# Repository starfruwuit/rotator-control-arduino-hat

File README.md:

# rotator-control-arduino-hat
hat to fit onto an Arduino MEGA 2560 R3 to connect a YAESU G550 rotator controller to input from SatNOGS
note: breadboard version uses 2N 2222 331 transistors: https://infodatasheet.com/2n2222a-331-datasheet.html

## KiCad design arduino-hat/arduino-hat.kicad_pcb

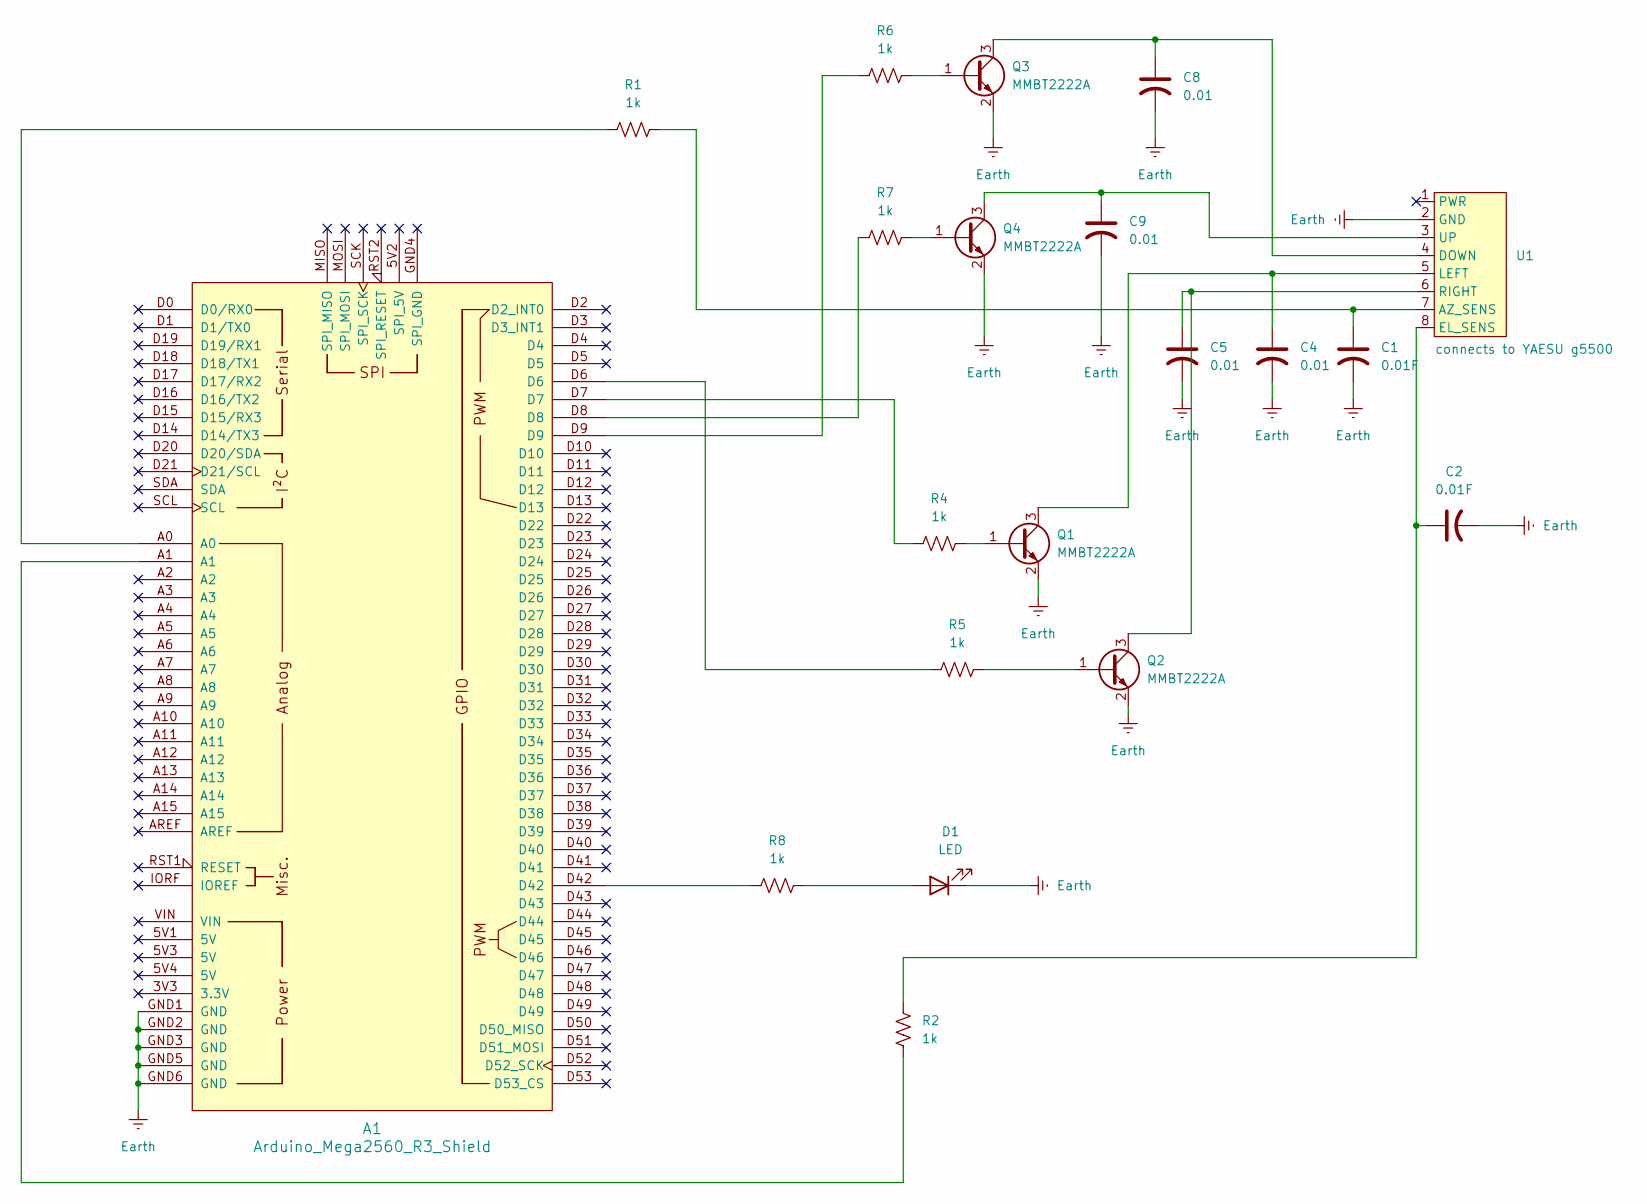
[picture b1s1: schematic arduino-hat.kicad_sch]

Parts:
A1: Arduino_Mega2560_R3_Shield; Arduino_Mega2560_R3_Shield_revised
C1, C2: 0.01F; C_0805_2012Metric_Pad1.18x1.45mm_HandSolder
C4, C5, C8, C9: 0.01; C_0805_2012Metric_Pad1.18x1.45mm_HandSolder
D1: LED; LED_1206_3216Metric_Pad1.42x1.75mm_HandSolder
Q1, Q2, Q3, Q4: MMBT2222A; SOT-23
R1, R2, R4, R5, R6, R7, R8: 1k; R_0603_1608Metric_Pad0.98x0.95mm_HandSolder
U1: PinHeader_1x08_P2.54mm_Vertical

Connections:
Earth: A1.GND1 (GND), A1.GND2 (GND), A1.GND3 (GND), A1.GND5 (GND), A1.GND6 (GND), C1.2, C2.2, C4.2, C5.2, C8.2, C9.2, D1.1 (K), Q1.2 (E), Q2.2 (E), Q3.2 (E), Q4.2 (E), U1.2 (GND)
unnamed: A1.A0, R1.1
unnamed: A1.A1, R2.2
unnamed: A1.D6, R5.1
unnamed: A1.D7, R4.1
unnamed: A1.D8, R7.1
unnamed: A1.D9, R6.1
unnamed: A1.D42, R8.2
unnamed: D1.2 (A), R8.1
unnamed: Q1.1 (B), R4.2
unnamed: C4.1, Q1.3 (C), U1.5 (LEFT)
unnamed: Q2.1 (B), R5.2
unnamed: C5.1, Q2.3 (C), U1.6 (RIGHT)
unnamed: Q3.1 (B), R6.2
unnamed: C8.1, Q3.3 (C), U1.4 (DOWN)
unnamed: Q4.1 (B), R7.2
unnamed: C9.1, Q4.3 (C), U1.3 (UP)
unnamed: C1.1, R1.2, U1.7 (AZ_SENS)
unnamed: C2.1, R2.1, U1.8 (EL_SENS)

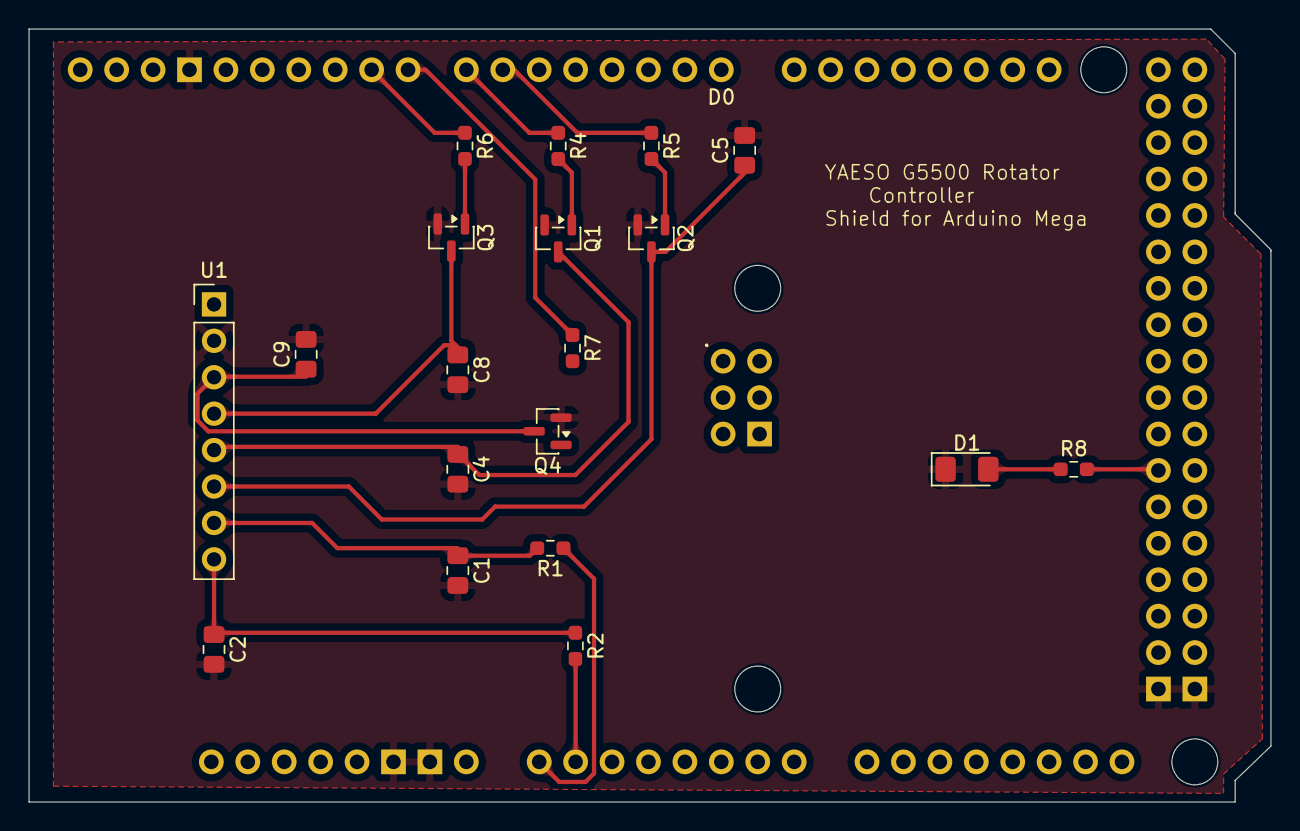
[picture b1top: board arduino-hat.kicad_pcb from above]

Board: 2 copper layers, 86.6 x 53.9 mm, 20 parts (0 on the bottom side), 19 nets.

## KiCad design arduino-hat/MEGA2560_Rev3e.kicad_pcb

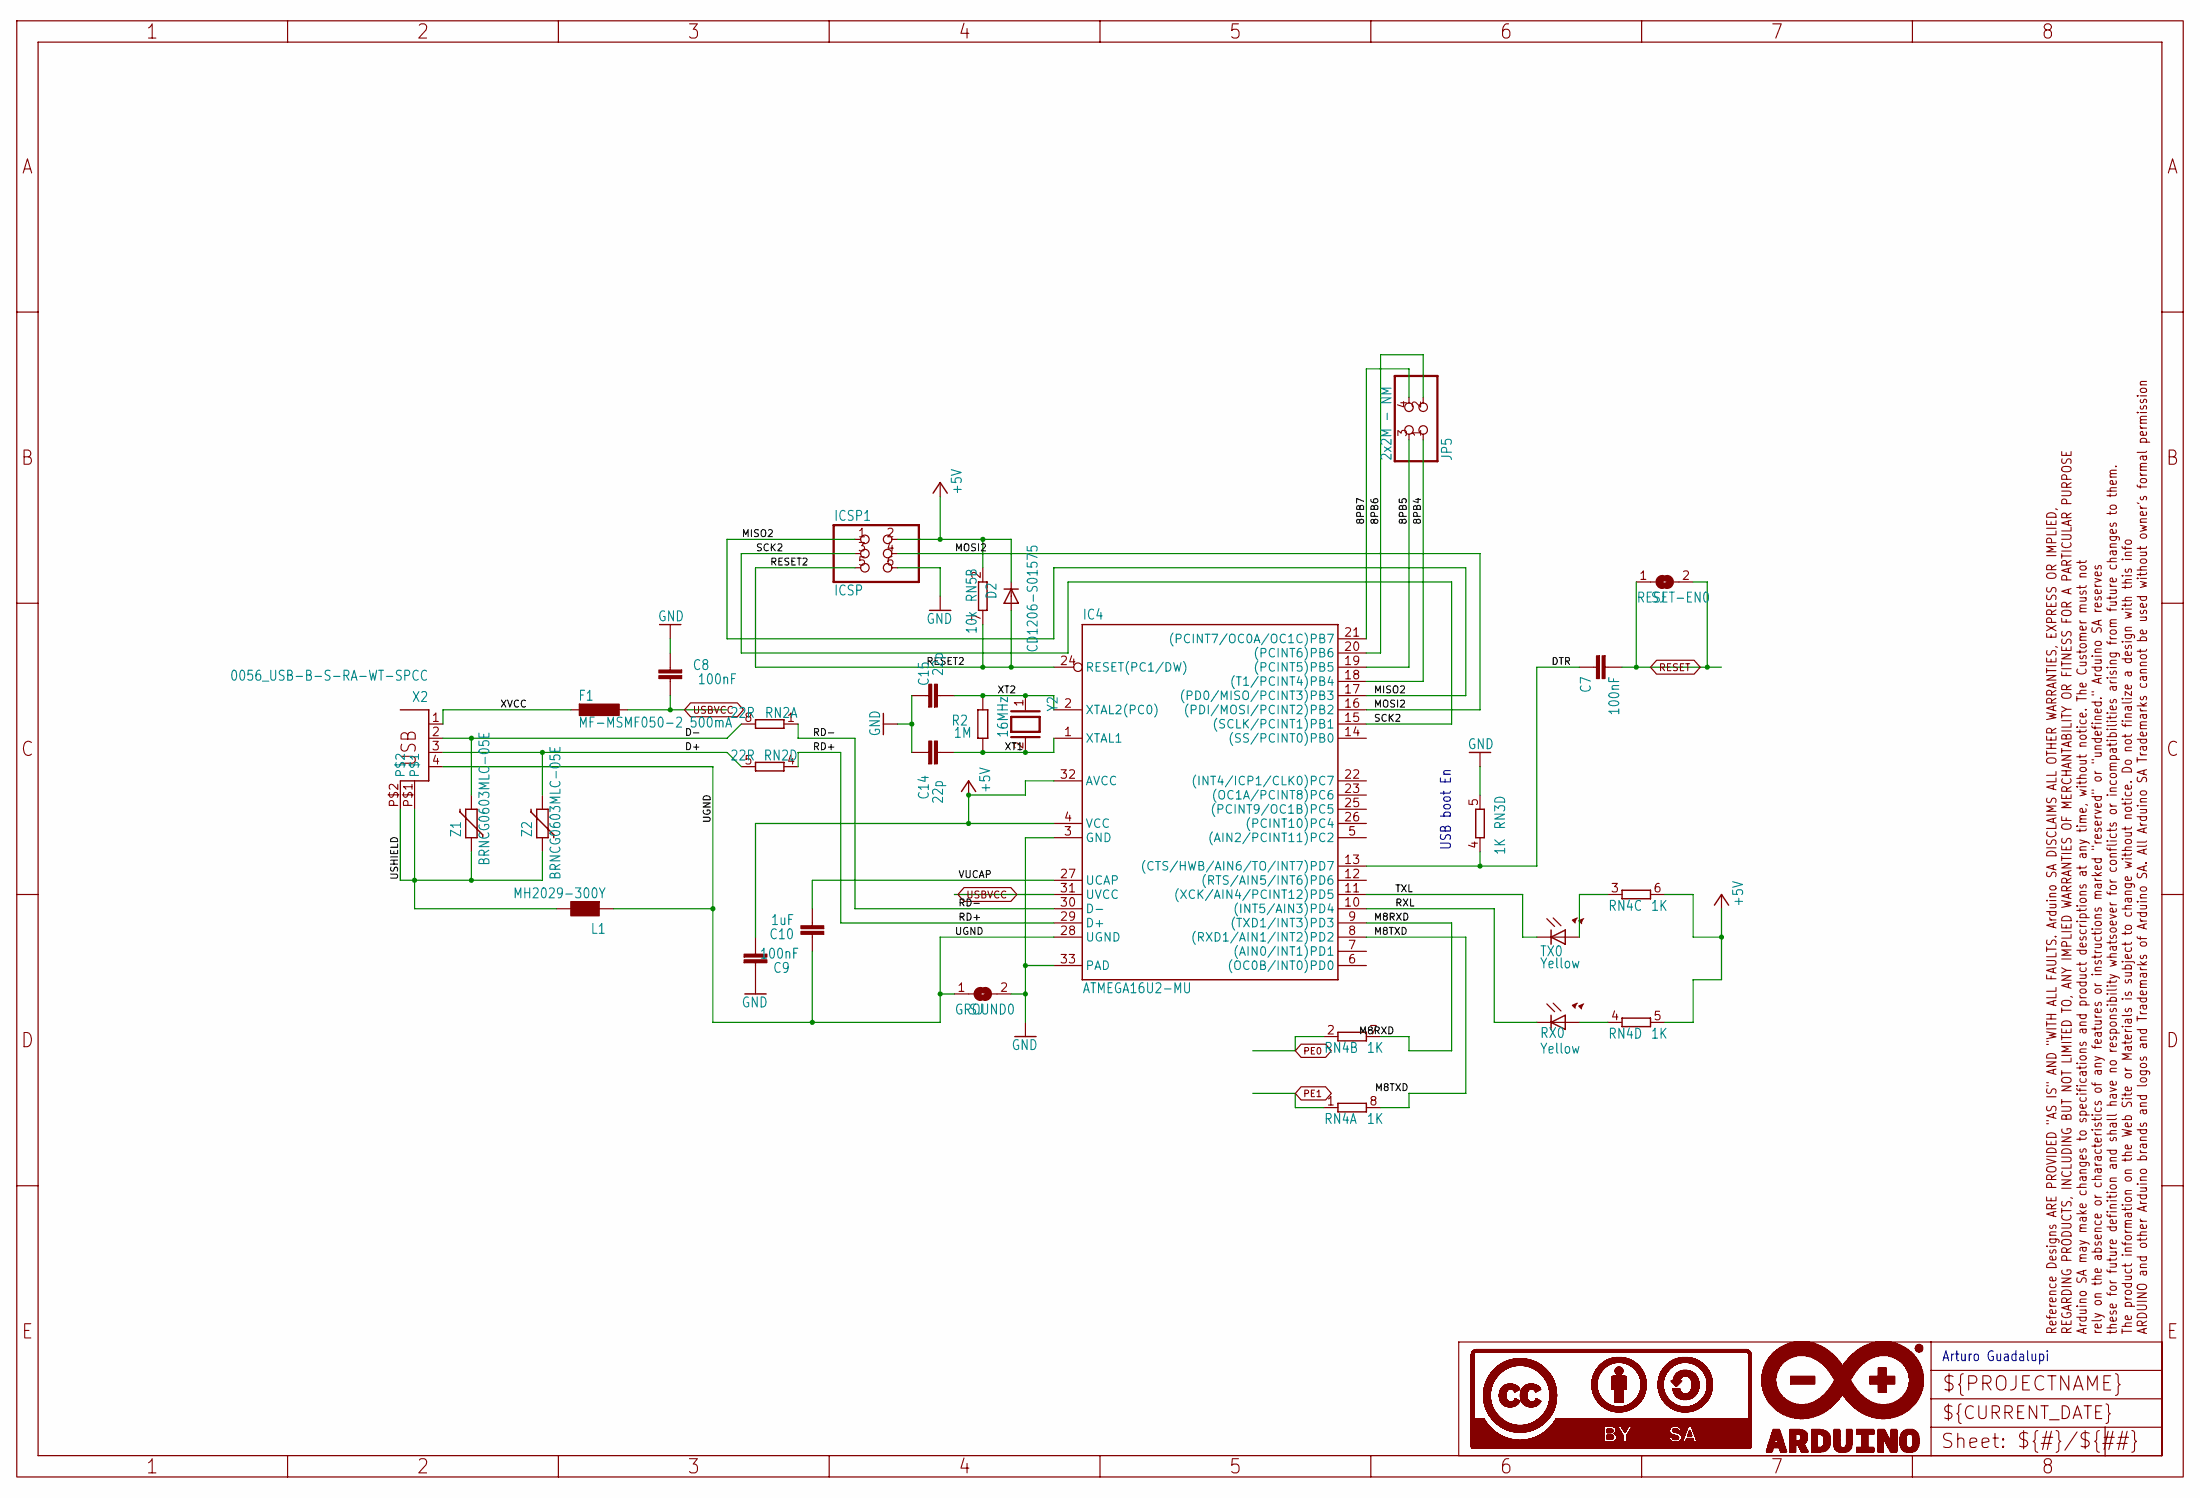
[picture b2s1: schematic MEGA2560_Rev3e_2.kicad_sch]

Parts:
C7, C8, C9: 100nF; C0603-ROUND
C10: 1uF; C0603-ROUND
C14, C15: 22p; C0603-ROUND
D2: CD1206-S01575; MINIMELF
F1: MF-MSMF050-2 500mA; L1812
GROUND0: SJ
IC4: ATMEGA16U2-MU; MLF32
ICSP1: ICSP; 2X03
JP5: 2x2M - NM; 2X02
L1: MH2029-300Y; 0805
R2: 1M; R0603-ROUND
RESET-EN0: SJ
RN2: 22R; CAY16
RN3, RN4: 1K; CAY16
RN5: 10k; CAY16
RX0: Yellow; CHIPLED_0805
TX0: Yellow; CHIPLED_0805
U$2: DNP; FRAME
X2: 0056_USB-B-S-RA-WT-SPCC; PN61729
Y2: 16MHz; QS
Z1, Z2: BRNCG0603MLC-05E; CT_CN0603

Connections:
8PB4: IC4.18 ((T1/PCINT4)PB4), JP5.1
8PB5: IC4.19 ((PCINT5)PB5), JP5.3
8PB6: IC4.20 ((PCINT6)PB6), JP5.2
8PB7: IC4.21 ((PCINT7/OC0A/OC1C)PB7), JP5.4
+5V: C9.1, D2.C, IC4.4 (VCC), IC4.32 (AVCC), ICSP1.2, RN4.5 (2), RN4.6 (2), RN5.2 (1); also elsewhere on the board
D+: RN2.5 (2), X2.3, Z2.2
D-: RN2.8 (2), X2.2, Z1.2
DTR: C7.1, IC4.13 ((CTS/HWB/AIN6/TO/INT7)PD7), RN3.4 (1)
GND: C8.2, C9.2, C14.2, C15.2, GROUND0.2, IC4.3 (GND), IC4.33 (PAD), ICSP1.6, RN3.5 (2); also elsewhere on the board
M8RXD: IC4.9 ((TXD1/INT3)PD3), RN4.7 (2)
M8TXD: IC4.8 ((RXD1/AIN1/INT2)PD2), RN4.8 (2)
MISO2: IC4.17 ((PD0/MISO/PCINT3)PB3), ICSP1.1
MOSI2: IC4.16 ((PDI/MOSI/PCINT2)PB2), ICSP1.4
unnamed: RN4.4 (1), RX0.A
unnamed: RN4.3 (1), TX0.A
PE0: RN4.2 (1); also elsewhere on the board
PE1: RN4.1; also elsewhere on the board
RD+: IC4.29 (D+), RN2.4 (1)
RD-: IC4.30 (D-), RN2.1
RESET: C7.2, RESET-EN0.1, RESET-EN0.2; also elsewhere on the board
RESET2: D2.A, IC4.24 (RESET(PC1/DW)), ICSP1.5, RN5.7 (2)
RXL: IC4.10 ((INT5/AIN3)PD4), RX0.C
SCK2: IC4.15 ((SCLK/PCINT1)PB1), ICSP1.3
TXL: IC4.11 ((XCK/AIN4/PCINT12)PD5), TX0.C
UGND: C10.2, GROUND0.1, IC4.28 (UGND), L1.1, X2.4
USBVCC: C8.1, F1.1, IC4.31 (UVCC); also elsewhere on the board
USHIELD: L1.2, X2.P$1, X2.P$2, Z1.1, Z2.1
VUCAP: C10.1, IC4.27 (UCAP)
XT1: C14.1, IC4.1 (XTAL1), R2.1, Y2.2
XT2: C15.1, IC4.2 (XTAL2(PC0)), R2.2, Y2.1
XVCC: F1.2, X2.1

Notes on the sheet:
USB boot En
Arturo Guadalupi

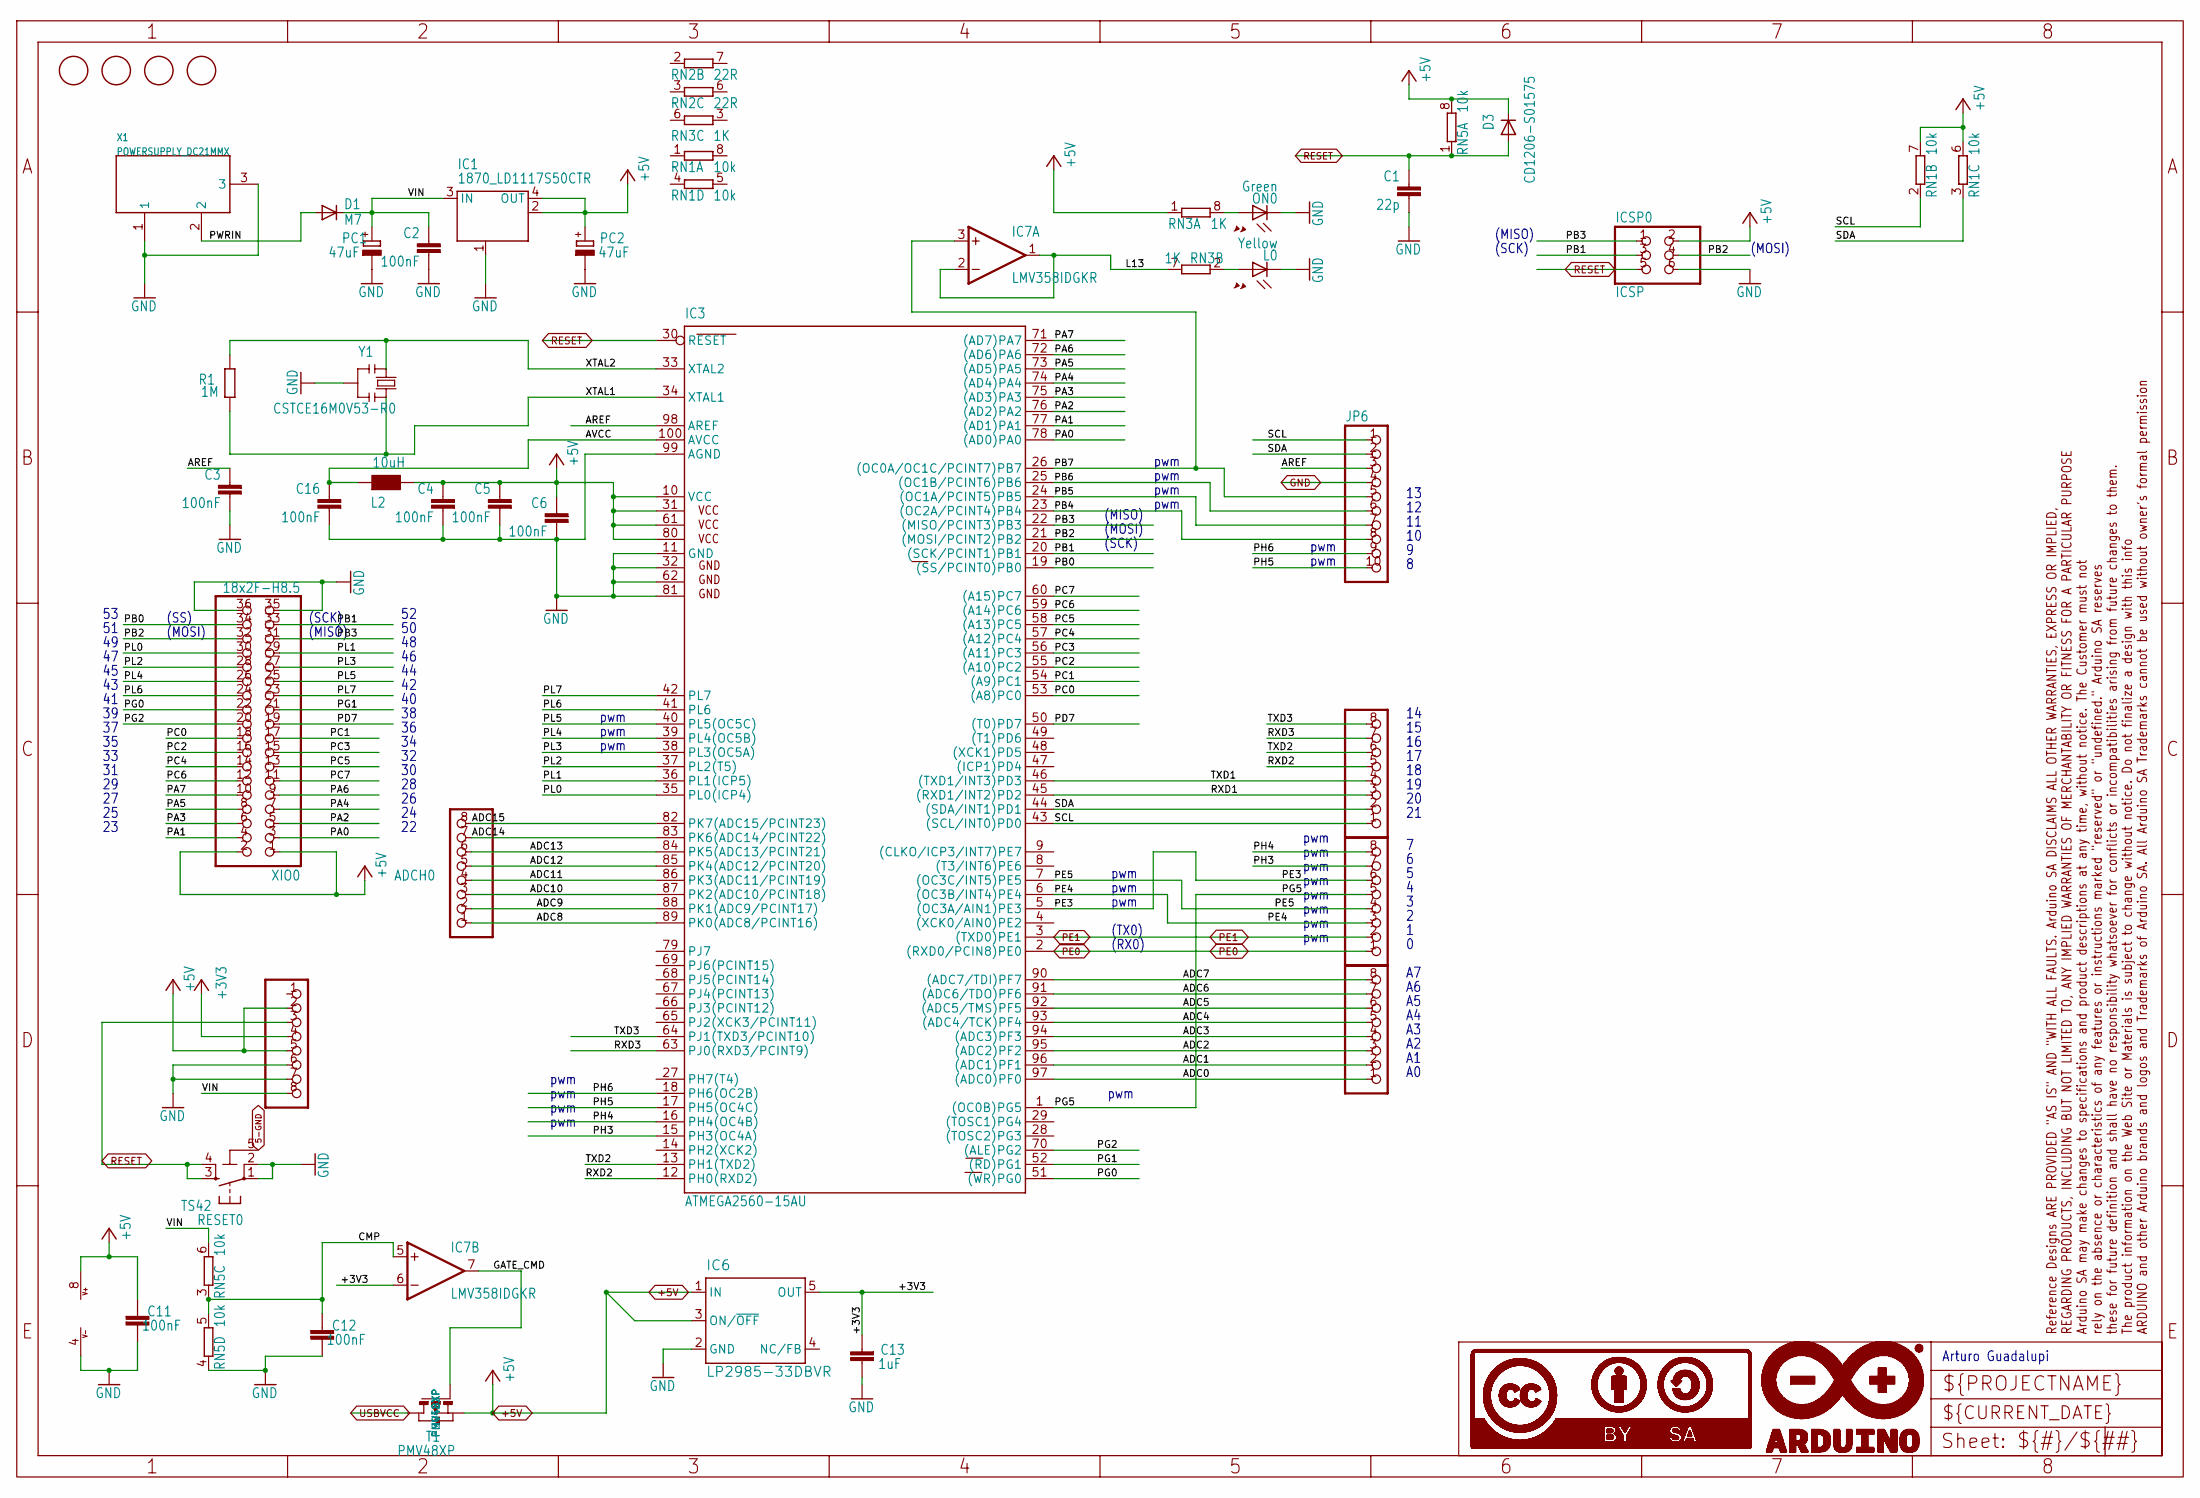
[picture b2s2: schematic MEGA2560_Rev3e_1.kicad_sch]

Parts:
ADCH0: FH254-108DF08500V; 1X08
ADCL0: FH254-108DF08500V; 1X08
C1: 22p; C0603-ROUND
C2, C3, C4, C5, C6, C11, C12, C16: 100nF; C0603-ROUND
C13: 1uF; C0603-ROUND
COMMUNICATION0: FH254-108DF08500V; 1X08
D1: M7; SMB
D3: CD1206-S01575; MINIMELF
FD1, FD2, FD3, FD4: FIDUCIALMOUNT; FIDUCIA-MOUNT
IC1: 1870_LD1117S50CTR; LINEAR_SOT223
IC3: ATMEGA2560-15AU; TQFP100
IC6: LP2985-33DBVR; SOT23-DBV
IC7: LMV358IDGKR; MSOP08
ICSP0: ICSP; 2X03
JP6: FH254-110DF08500V; 1X10
L0: Yellow; CHIPLED_0805
L2: 10uH; 0805
ON0: Green; CHIPLED_0805
PC1, PC2: 47uF; PANASONIC_D
POWER0: FH254-108DF08500V; 1X08
PWML0: FH254-108DF08500V; 1X08
R1: 1M; R0603-ROUND
RESET0: TS42
RN1, RN5: 10k; CAY16
RN2: 22R; CAY16
RN3: 1K; CAY16
T1: PMV48XP; SOT-23; PART_NUMBER PMV48XP
U$1: DNP; FRAME
X1: POWERSUPPLY_DC21MMX; POWERSUPPLY_DC-21MM
XIO0: 18x2F-H8.5; 2X18
Y1: CSTCE16M0V53-R0; RESONATOR

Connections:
5-GND: RESET0.5 (5-GND)
+3V3: C13.2, IC6.5 (OUT), IC7.6 (-IN), POWER0.4
+5V: C4.1, C5.1, C6.1, C11.2, D3.C, IC1.2 (OUT@1), IC1.4 (OUT), IC3.10 (VCC), IC3.31 (VCC1), IC3.61 (VCC2), IC3.80 (VCC3), IC6.1 (IN), IC6.3 (ON/~OFF), IC7.8 (V+), ICSP0.2, L2.2, PC2.+, POWER0.2, POWER0.5, RN1.6 (2), RN1.7 (2), RN3.1, RN5.8 (2), T1.2 (S), XIO0.1, XIO0.2; also elsewhere on the board
ADC0: ADCL0.1, IC3.97 ((ADC0)PF0)
ADC1: ADCL0.2, IC3.96 ((ADC1)PF1)
ADC2: ADCL0.3, IC3.95 ((ADC2)PF2)
ADC3: ADCL0.4, IC3.94 ((ADC3)PF3)
ADC4: ADCL0.5, IC3.93 ((ADC4/TCK)PF4)
ADC5: ADCL0.6, IC3.92 ((ADC5/TMS)PF5)
ADC6: ADCL0.7, IC3.91 ((ADC6/TDO)PF6)
ADC7: ADCL0.8, IC3.90 ((ADC7/TDI)PF7)
ADC8: ADCH0.1, IC3.89 (PK0(ADC8/PCINT16))
ADC9: ADCH0.2, IC3.88 (PK1(ADC9/PCINT17))
ADC10: ADCH0.3, IC3.87 (PK2(ADC10/PCINT18))
ADC11: ADCH0.4, IC3.86 (PK3(ADC11/PCINT19))
ADC12: ADCH0.5, IC3.85 (PK4(ADC12/PCINT20))
ADC13: ADCH0.6, IC3.84 (PK5(ADC13/PCINT21))
ADC14: ADCH0.7, IC3.83 (PK6(ADC14/PCINT22))
ADC15: ADCH0.8, IC3.82 (PK7(ADC15/PCINT23))
AREF: C3.1, IC3.98 (AREF), JP6.3
AVCC: C16.1, IC3.100 (AVCC), L2.1
CMP: C12.2, IC7.5 (+IN), RN5.3 (1), RN5.5 (2)
GATE_CMD: IC7.7 (OUT), T1.3 (G)
GND: C1.2, C2.2, C3.2, C4.2, C5.2, C6.2, C11.1, C12.1, C13.1, C16.2, IC1.1 (GND/ADJ), IC3.11 (GND), IC3.32 (GND1), IC3.62 (GND2), IC3.81 (GND3), IC3.99 (AGND), IC6.2 (GND), IC7.4 (V-), ICSP0.6, JP6.4, L0.C, ON0.C, PC1.-, PC2.-, POWER0.6, POWER0.7, RESET0.1, RESET0.2, RN5.4 (1), X1.1, X1.3, XIO0.35, XIO0.36, Y1.2; also elsewhere on the board
L13: IC7.1 (OUT), IC7.2 (-IN), RN3.7 (2)
unnamed: L0.A, RN3.2 (1)
unnamed: ON0.A, RN3.8 (2)
PA0: IC3.78 ((AD0)PA0), XIO0.3
PA1: IC3.77 ((AD1)PA1), XIO0.4
PA2: IC3.76 ((AD2)PA2), XIO0.5
PA3: IC3.75 ((AD3)PA3), XIO0.6
PA4: IC3.74 ((AD4)PA4), XIO0.7
PA5: IC3.73 ((AD5)PA5), XIO0.8
PA6: IC3.72 ((AD6)PA6), XIO0.9
PA7: IC3.71 ((AD7)PA7), XIO0.10
PB0: IC3.19 ((SS/PCINT0)PB0), XIO0.34
PB1: IC3.20 ((SCK/PCINT1)PB1), ICSP0.3, XIO0.33
PB2: IC3.21 ((MOSI/PCINT2)PB2), ICSP0.4, XIO0.32
PB3: IC3.22 ((MISO/PCINT3)PB3), ICSP0.1, XIO0.31
PB4: IC3.23 ((OC2A/PCINT4)PB4), JP6.8
PB5: IC3.24 ((OC1A/PCINT5)PB5), JP6.7
PB6: IC3.25 ((OC1B/PCINT6)PB6), JP6.6
PB7: IC3.26 ((OC0A/OC1C/PCINT7)PB7), IC7.3 (+IN), JP6.5
PC0: IC3.53 ((A8)PC0), XIO0.18
PC1: IC3.54 ((A9)PC1), XIO0.17
PC2: IC3.55 ((A10)PC2), XIO0.16
PC3: IC3.56 ((A11)PC3), XIO0.15
PC4: IC3.57 ((A12)PC4), XIO0.14
PC5: IC3.58 ((A13)PC5), XIO0.13
PC6: IC3.59 ((A14)PC6), XIO0.12
PC7: IC3.60 ((A15)PC7), XIO0.11
PD7: IC3.50 ((T0)PD7), XIO0.19
PE0: IC3.2 ((RXD0/PCIN8)PE0), PWML0.1; also elsewhere on the board
PE1: IC3.3 ((TXD0)PE1), PWML0.2; also elsewhere on the board
PE3: IC3.5 ((OC3A/AIN1)PE3), PWML0.6
PE4: IC3.6 ((OC3B/INT4)PE4), PWML0.3
PE5: IC3.7 ((OC3C/INT5)PE5), PWML0.4
PG0: IC3.51 ((WR)PG0), XIO0.22
PG1: IC3.52 ((RD)PG1), XIO0.21
PG2: IC3.70 ((ALE)PG2), XIO0.20
PG5: IC3.1 ((OC0B)PG5), PWML0.5
PH3: IC3.15 (PH3(OC4A)), PWML0.7
PH4: IC3.16 (PH4(OC4B)), PWML0.8
PH5: IC3.17 (PH5(OC4C)), JP6.10
PH6: IC3.18 (PH6(OC2B)), JP6.9
PL0: IC3.35 (PL0(ICP4)), XIO0.30
PL1: IC3.36 (PL1(ICP5)), XIO0.29
PL2: IC3.37 (PL2(T5)), XIO0.28
PL3: IC3.38 (PL3(OC5A)), XIO0.27
PL4: IC3.39 (PL4(OC5B)), XIO0.26
PL5: IC3.40 (PL5(OC5C)), XIO0.25
PL6: IC3.41 (PL6), XIO0.24
PL7: IC3.42 (PL7), XIO0.23
PWRIN: D1.A, X1.2
RESET: C1.1, D3.A, IC3.30 (RESET), ICSP0.5, POWER0.3, RESET0.3, RESET0.4, RN5.1; also elsewhere on the board
RXD1: COMMUNICATION0.3, IC3.45 ((RXD1/INT2)PD2)
RXD2: COMMUNICATION0.5, IC3.12 (PH0(RXD2))
RXD3: COMMUNICATION0.7, IC3.63 (PJ0(RXD3/PCINT9))
SCL: COMMUNICATION0.1, IC3.43 ((SCL/INT0)PD0), JP6.1, RN1.2 (1)
SDA: COMMUNICATION0.2, IC3.44 ((SDA/INT1)PD1), JP6.2, RN1.3 (1)
TXD1: COMMUNICATION0.4, IC3.46 ((TXD1/INT3)PD3)
TXD2: COMMUNICATION0.6, IC3.13 (PH1(TXD2))
TXD3: COMMUNICATION0.8, IC3.64 (PJ1(TXD3/PCINT10))
USBVCC: T1.1 (D); also elsewhere on the board
VIN: C2.1, D1.C, IC1.3 (IN), PC1.+, POWER0.8, RN5.6 (2)
XTAL1: IC3.34 (XTAL1), R1.1, Y1.3
XTAL2: IC3.33 (XTAL2), R1.2, Y1.1

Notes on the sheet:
(MISO)
pwm
(MOSI)
(TX0)
(SCK)
Arturo Guadalupi
(SS)
(RX0)

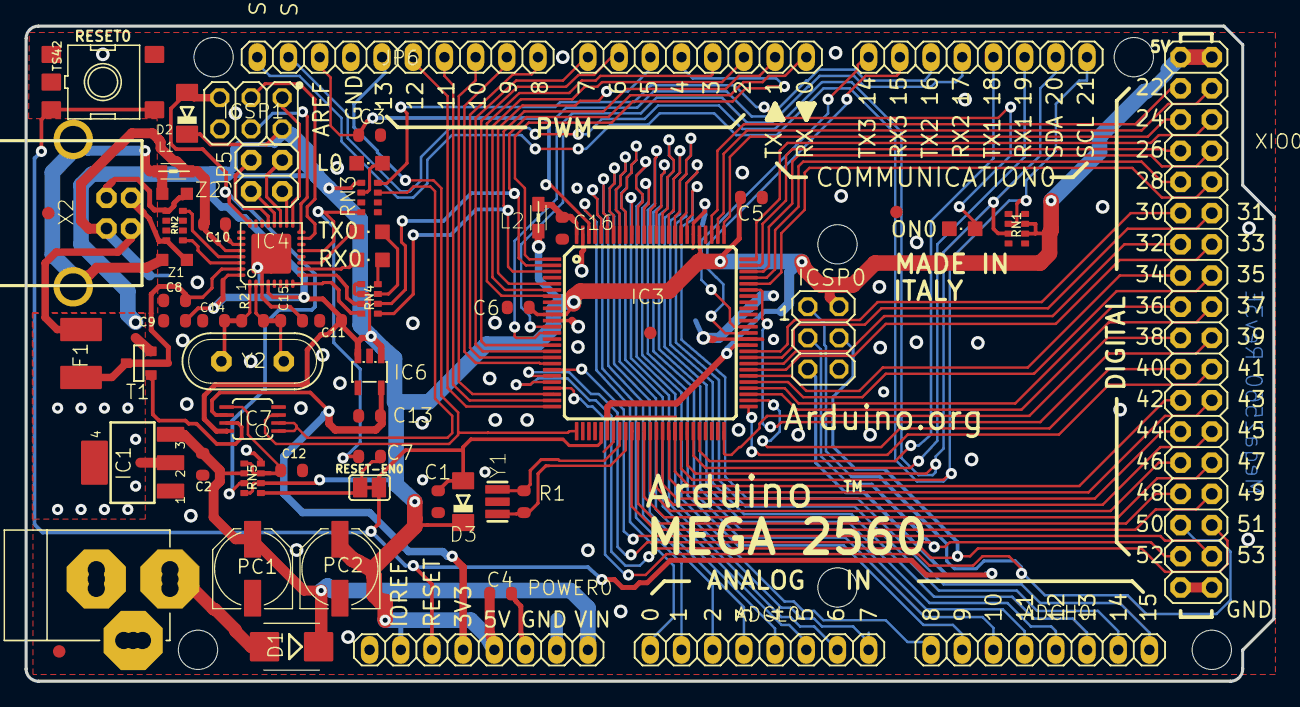
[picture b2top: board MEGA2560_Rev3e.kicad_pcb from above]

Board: 2 copper layers, 101.6 x 53.3 mm, 72 parts (1 on the bottom side), 111 nets.

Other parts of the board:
UNK_HOLE_0: dummyfp0
UNK_HOLE_1: dummyfp1
UNK_HOLE_2: dummyfp2
UNK_HOLE_3: dummyfp3
UNK_HOLE_4: dummyfp4
UNK_HOLE_5: dummyfp5

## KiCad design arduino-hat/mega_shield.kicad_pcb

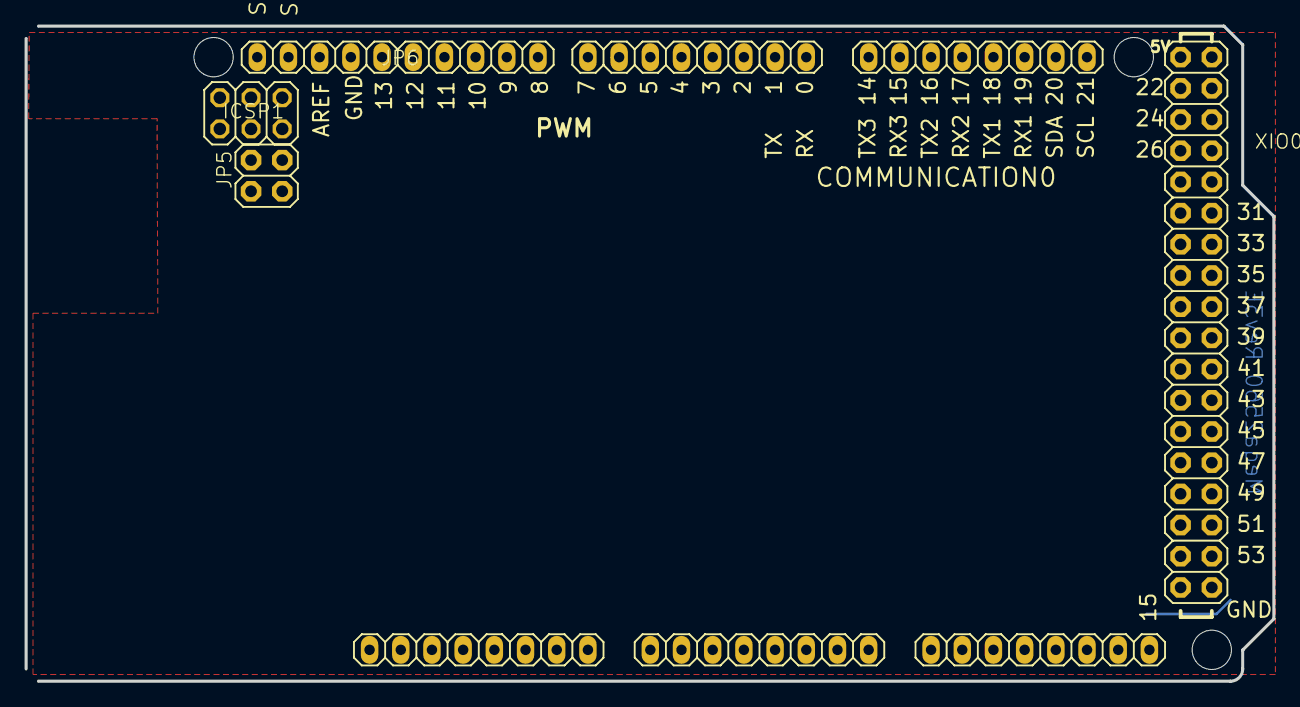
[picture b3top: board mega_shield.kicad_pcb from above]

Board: 2 copper layers, 101.6 x 53.3 mm, 14 parts (0 on the bottom side), 4 nets.

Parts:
ADCH0: FH254-108DF08500V; 1X08
ADCL0: FH254-108DF08500V; 1X08
COMMUNICATION0: FH254-108DF08500V; 1X08
ICSP1: ICSP; 2X03
JP5: 2x2M - NM; 2X02
JP6: FH254-110DF08500V; 1X10
POWER0: FH254-108DF08500V; 1X08
PWML0: FH254-108DF08500V; 1X08
U$1, U$2: DNP; FRAME
UNK_HOLE_0: dummyfp0
UNK_HOLE_1: dummyfp1
UNK_HOLE_2: dummyfp2
XIO0: 18x2F-H8.5; 2X18

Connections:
+5V: ICSP1.2, POWER0.2, POWER0.5, XIO0.1, XIO0.2
GND: ICSP1.6, JP6.4, POWER0.6, POWER0.7, XIO0.35, XIO0.36
SCL: COMMUNICATION0.1, JP6.1
SDA: COMMUNICATION0.2, JP6.2

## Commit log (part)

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2026-04-10 started kicad project
2026-06-04 imported arduino docs
2026-06-11 finished schematic?
2026-06-15 more PCB work
2026-06-25 PCB design semi-finalized
